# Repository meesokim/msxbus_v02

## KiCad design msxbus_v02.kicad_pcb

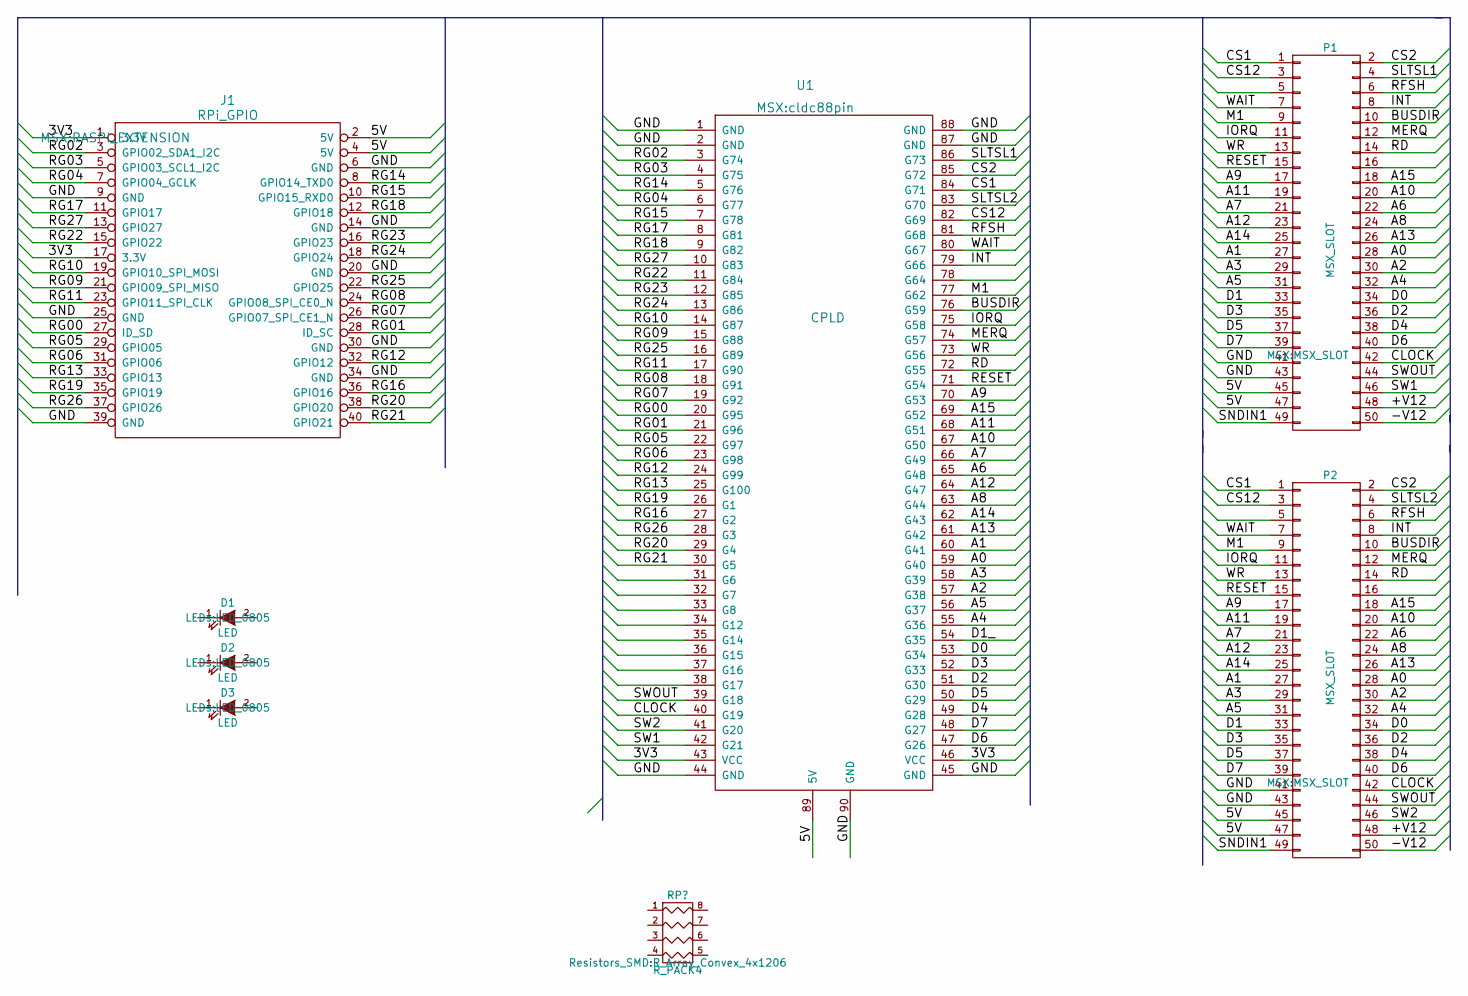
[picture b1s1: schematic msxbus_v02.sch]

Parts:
D1, D2, D3: LED; LED_0805
J1: RPi_GPIO; RASPI_EXTENSION
P1, P2: MSX_SLOT
U1: CPLD; cldc88pin

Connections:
/3V3: J1.1 (3.3V), J1.17 (3.3V), U1.43 (VCC), U1.46 (VCC)
/5V: J1.2 (5V), J1.4 (5V), P1.45, P1.47, P2.45, P2.47, U1.89 (5V)
/+V12: P1.48, P2.48
/-V12: P1.50, P2.50
/A0: P1.28, P2.28, U1.59 (G40)
/A1: P1.27, P2.27, U1.60 (G41)
/A2: P1.30, P2.30, U1.57 (G38)
/A3: P1.29, P2.29, U1.58 (G39)
/A4: P1.32, P2.32, U1.55 (G36)
/A5: P1.31, P2.31, U1.56 (G37)
/A6: P1.22, P2.22, U1.65 (G48)
/A7: P1.21, P2.21, U1.66 (G49)
/A8: P1.24, P2.24, U1.63 (G44)
/A9: P1.17, P2.17, U1.70 (G53)
/A10: P1.20, P2.20, U1.67 (G50)
/A11: P1.19, P2.19, U1.68 (G51)
/A12: P1.23, P2.23, U1.64 (G47)
/A13: P1.26, P2.26, U1.61 (G42)
/A14: P1.25, P2.25, U1.62 (G43)
/A15: P1.18, P2.18, U1.69 (G52)
/BUSDIR: P1.10, P2.10, U1.76 (G59)
/CLOCK: P1.42, P2.42, U1.40 (G19)
/CS1: P1.1 (CS1), P2.1 (CS1), U1.84 (G71)
/CS2: P1.2, P2.2, U1.85 (G72)
/CS12: P1.3, P2.3, U1.82 (G69)
/D0: P1.34, P2.34, U1.53 (G34)
/D1: P1.33, P2.33; also elsewhere on the board
/D1_: U1.54 (G35); also elsewhere on the board
/D2: P1.36, P2.36, U1.51 (G30)
/D3: P1.35, P2.35, U1.52 (G33)
/D4: P1.38, P2.38, U1.49 (G28)
/D5: P1.37, P2.37, U1.50 (G29)
/D6: P1.40, P2.40, U1.47 (G26)
/D7: P1.39, P2.39, U1.48 (G27)
/GND: J1.6 (GND), J1.9 (GND), J1.14 (GND), J1.20 (GND), J1.25 (GND), J1.30 (GND), J1.34 (GND), J1.39 (GND), P1.41, P1.43, P2.41, P2.43, U1.1 (GND), U1.2 (GND), U1.44 (GND), U1.45 (GND), U1.87 (GND), U1.88 (GND), U1.90 (GND)
/INT: P1.8, P2.8, U1.79 (G66)
/IORQ: P1.11, P2.11, U1.75 (G58)
/M1: P1.9, P2.9, U1.77 (G62)
/MERQ: P1.12, P2.12, U1.74 (G57)
/RD: P1.14, P2.14, U1.72 (G55)
/RESET: P1.15, P2.15, U1.71 (G54)
/RFSH: P1.6, P2.6, U1.81 (G68)
/RG00: J1.27 (ID_SD), U1.20 (G95)
/RG01: J1.28 (ID_SC), U1.21 (G96)
/RG02: J1.3 (GPIO02_SDA1_I2C), U1.3 (G74)
/RG03: J1.5 (GPIO03_SCL1_I2C), U1.4 (G75)
/RG04: J1.7 (GPIO04_GCLK), U1.6 (G77)
/RG05: J1.29 (GPIO05), U1.22 (G97)
/RG06: J1.31 (GPIO06), U1.23 (G98)
/RG07: J1.26 (GPIO07_SPI_CE1_N), U1.19 (G92)
/RG08: J1.24 (GPIO08_SPI_CE0_N), U1.18 (G91)
/RG09: J1.21 (GPIO09_SPI_MISO), U1.15 (G88)
/RG10: J1.19 (GPIO10_SPI_MOSI), U1.14 (G87)
/RG11: J1.23 (GPIO11_SPI_CLK), U1.17 (G90)
/RG12: J1.32 (GPIO12), U1.24 (G99)
/RG13: J1.33 (GPIO13), U1.25 (G100)
/RG14: J1.8 (GPIO14_TXD0), U1.5 (G76)
/RG15: J1.10 (GPIO15_RXD0), U1.7 (G78)
/RG16: J1.36 (GPIO16), U1.27 (G2)
/RG17: J1.11 (GPIO17), U1.8 (G81)
/RG18: J1.12 (GPIO18), U1.9 (G82)
/RG19: J1.35 (GPIO19), U1.26 (G1)
/RG20: J1.38 (GPIO20), U1.29 (G4)
/RG21: J1.40 (GPIO21), U1.30 (G5)
/RG22: J1.15 (GPIO22), U1.11 (G84)
/RG23: J1.16 (GPIO23), U1.12 (G85)
/RG24: J1.18 (GPIO24), U1.13 (G86)
/RG25: J1.22 (GPIO25), U1.16 (G89)
/RG26: J1.37 (GPIO26), U1.28 (G3)
/RG27: J1.13 (GPIO27), U1.10 (G83)
/SLTSL1: P1.4, U1.86 (G73)
/SLTSL2: P2.4, U1.83 (G70)
/SNDIN1: P1.49, P2.49
/SW1: P1.46, U1.42 (G21)
/SW2: P2.46, U1.41 (G20)
/SWOUT: P1.44, P2.44, U1.39 (G18)
/WAIT: P1.7, P2.7, U1.80 (G67)
/WR: P1.13, P2.13, U1.73 (G56)

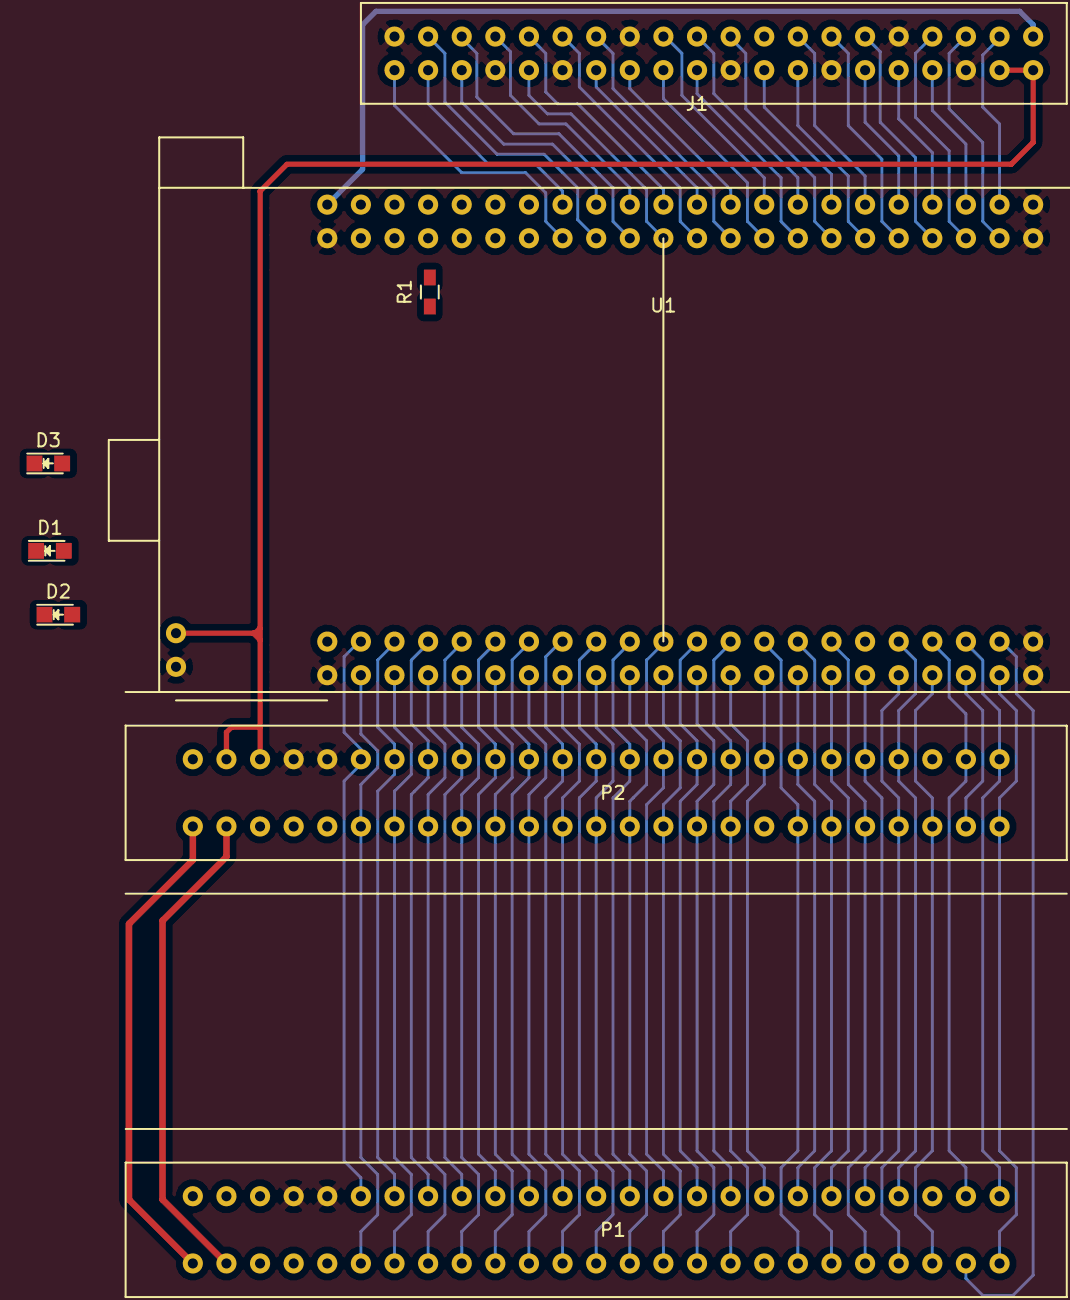
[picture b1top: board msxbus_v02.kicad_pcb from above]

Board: 2 copper layers, 8 parts (0 on the bottom side), 78 nets.

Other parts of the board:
R1: R; R_0603_HandSoldering

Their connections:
/D1: R1.2; also elsewhere on the board
/D1_: R1.1; also elsewhere on the board

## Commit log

2016-04-24 RPMC MSX Bus Slot v0.2
2016-05-01 PCB update
2016-05-03 minor update
